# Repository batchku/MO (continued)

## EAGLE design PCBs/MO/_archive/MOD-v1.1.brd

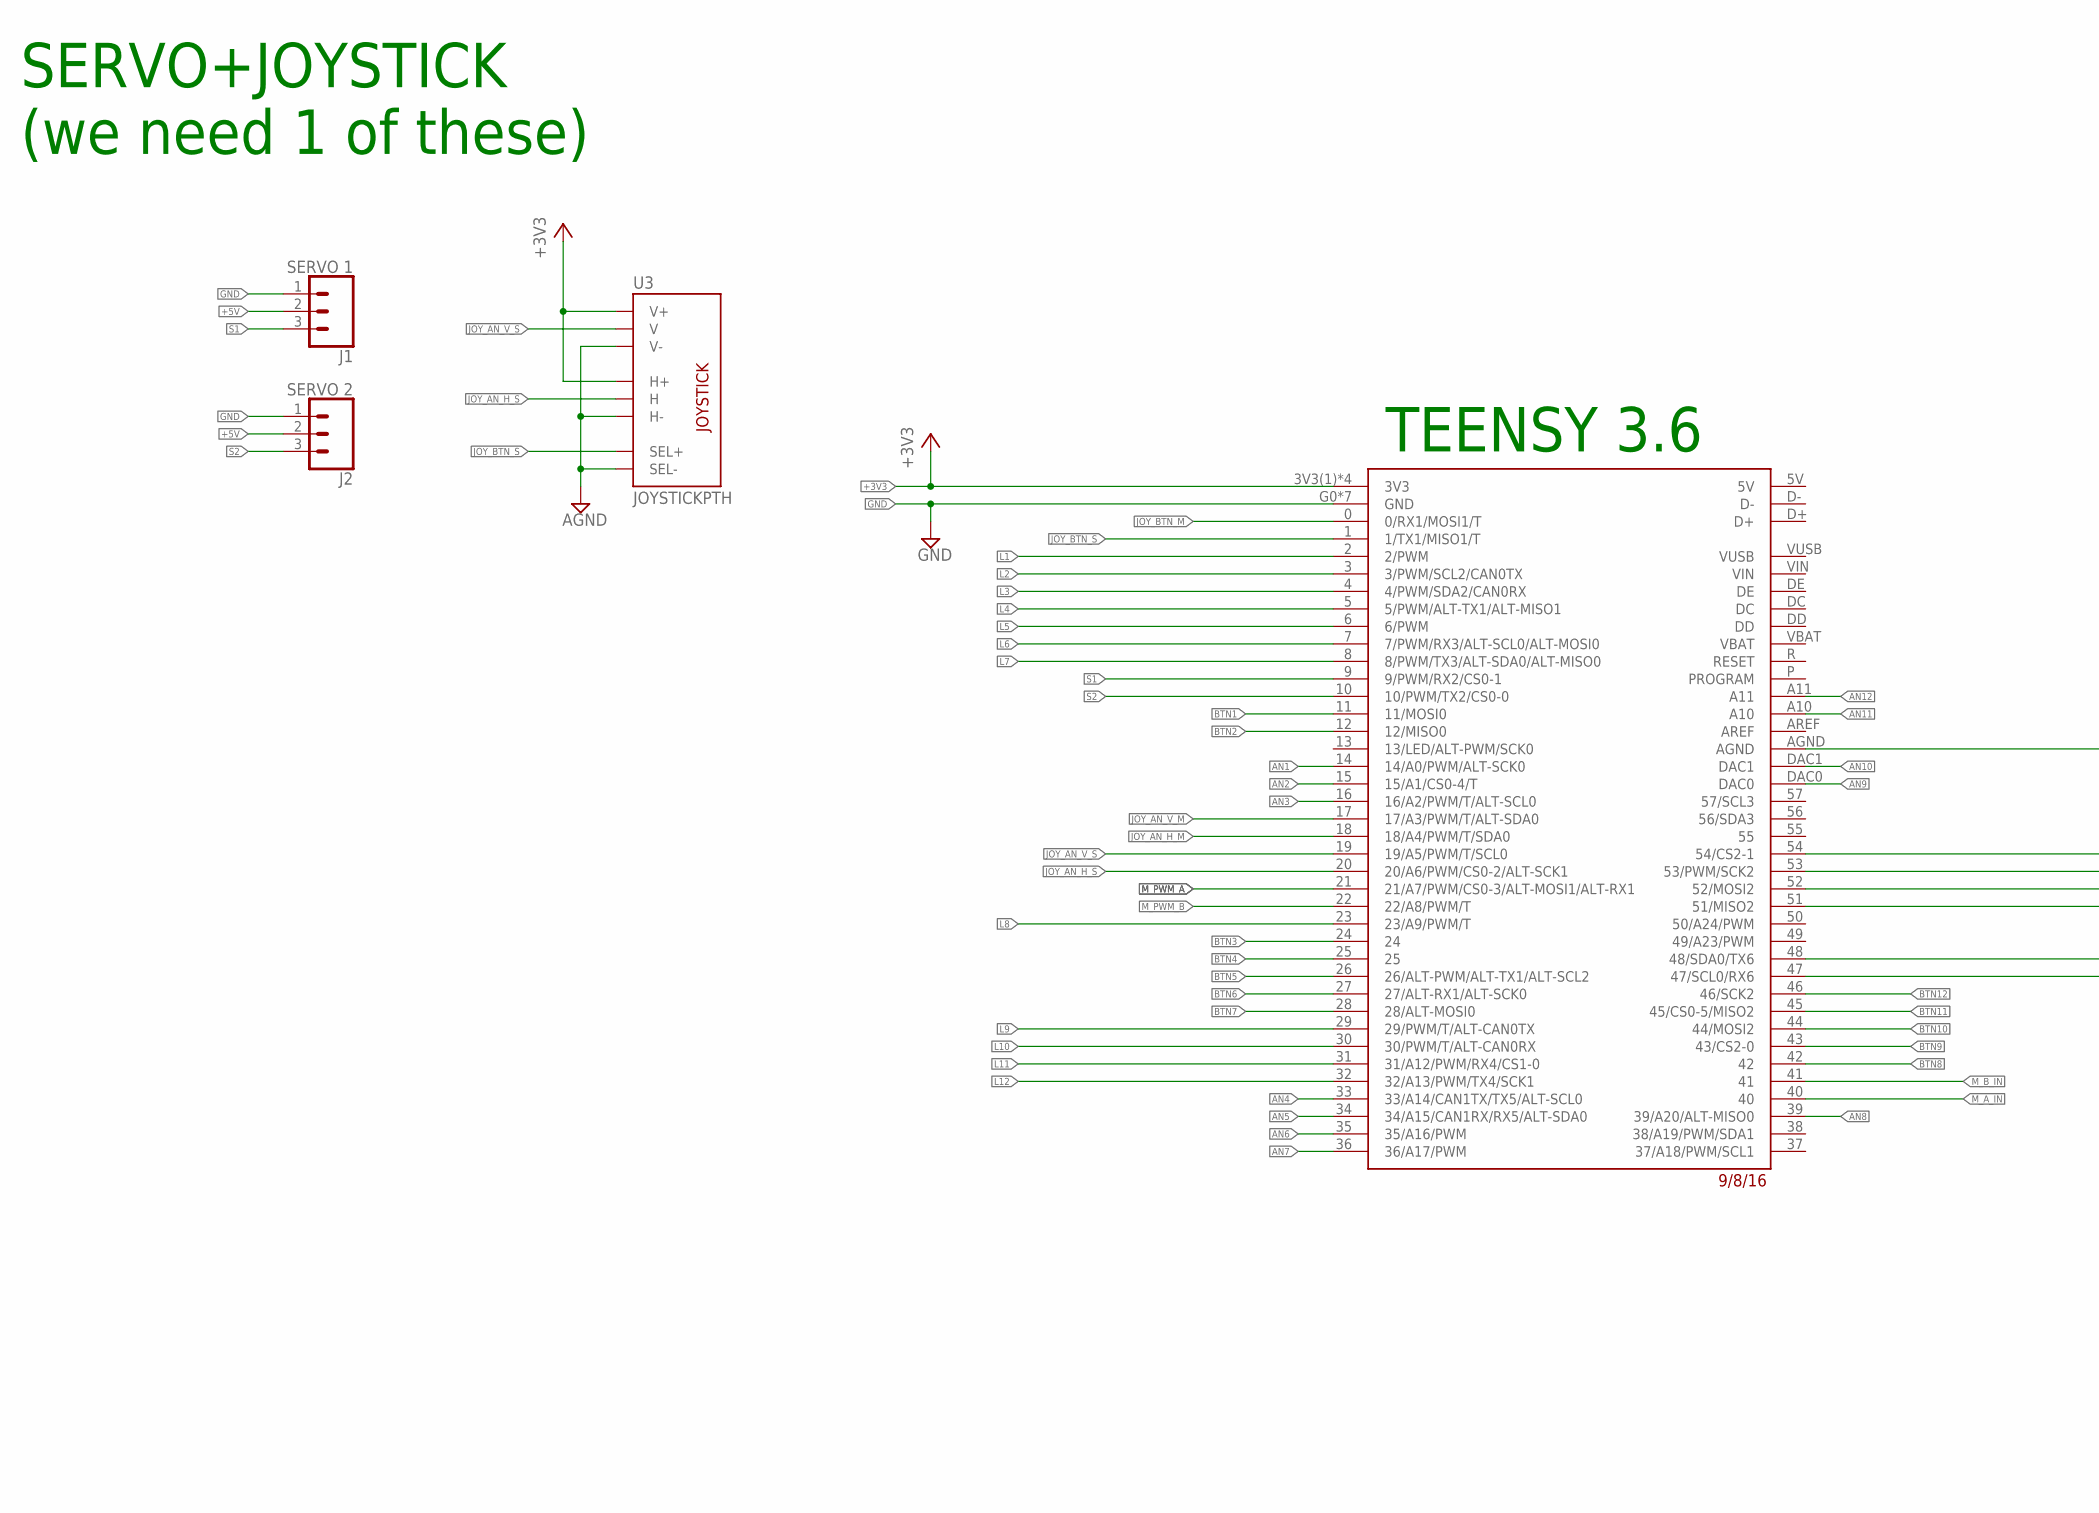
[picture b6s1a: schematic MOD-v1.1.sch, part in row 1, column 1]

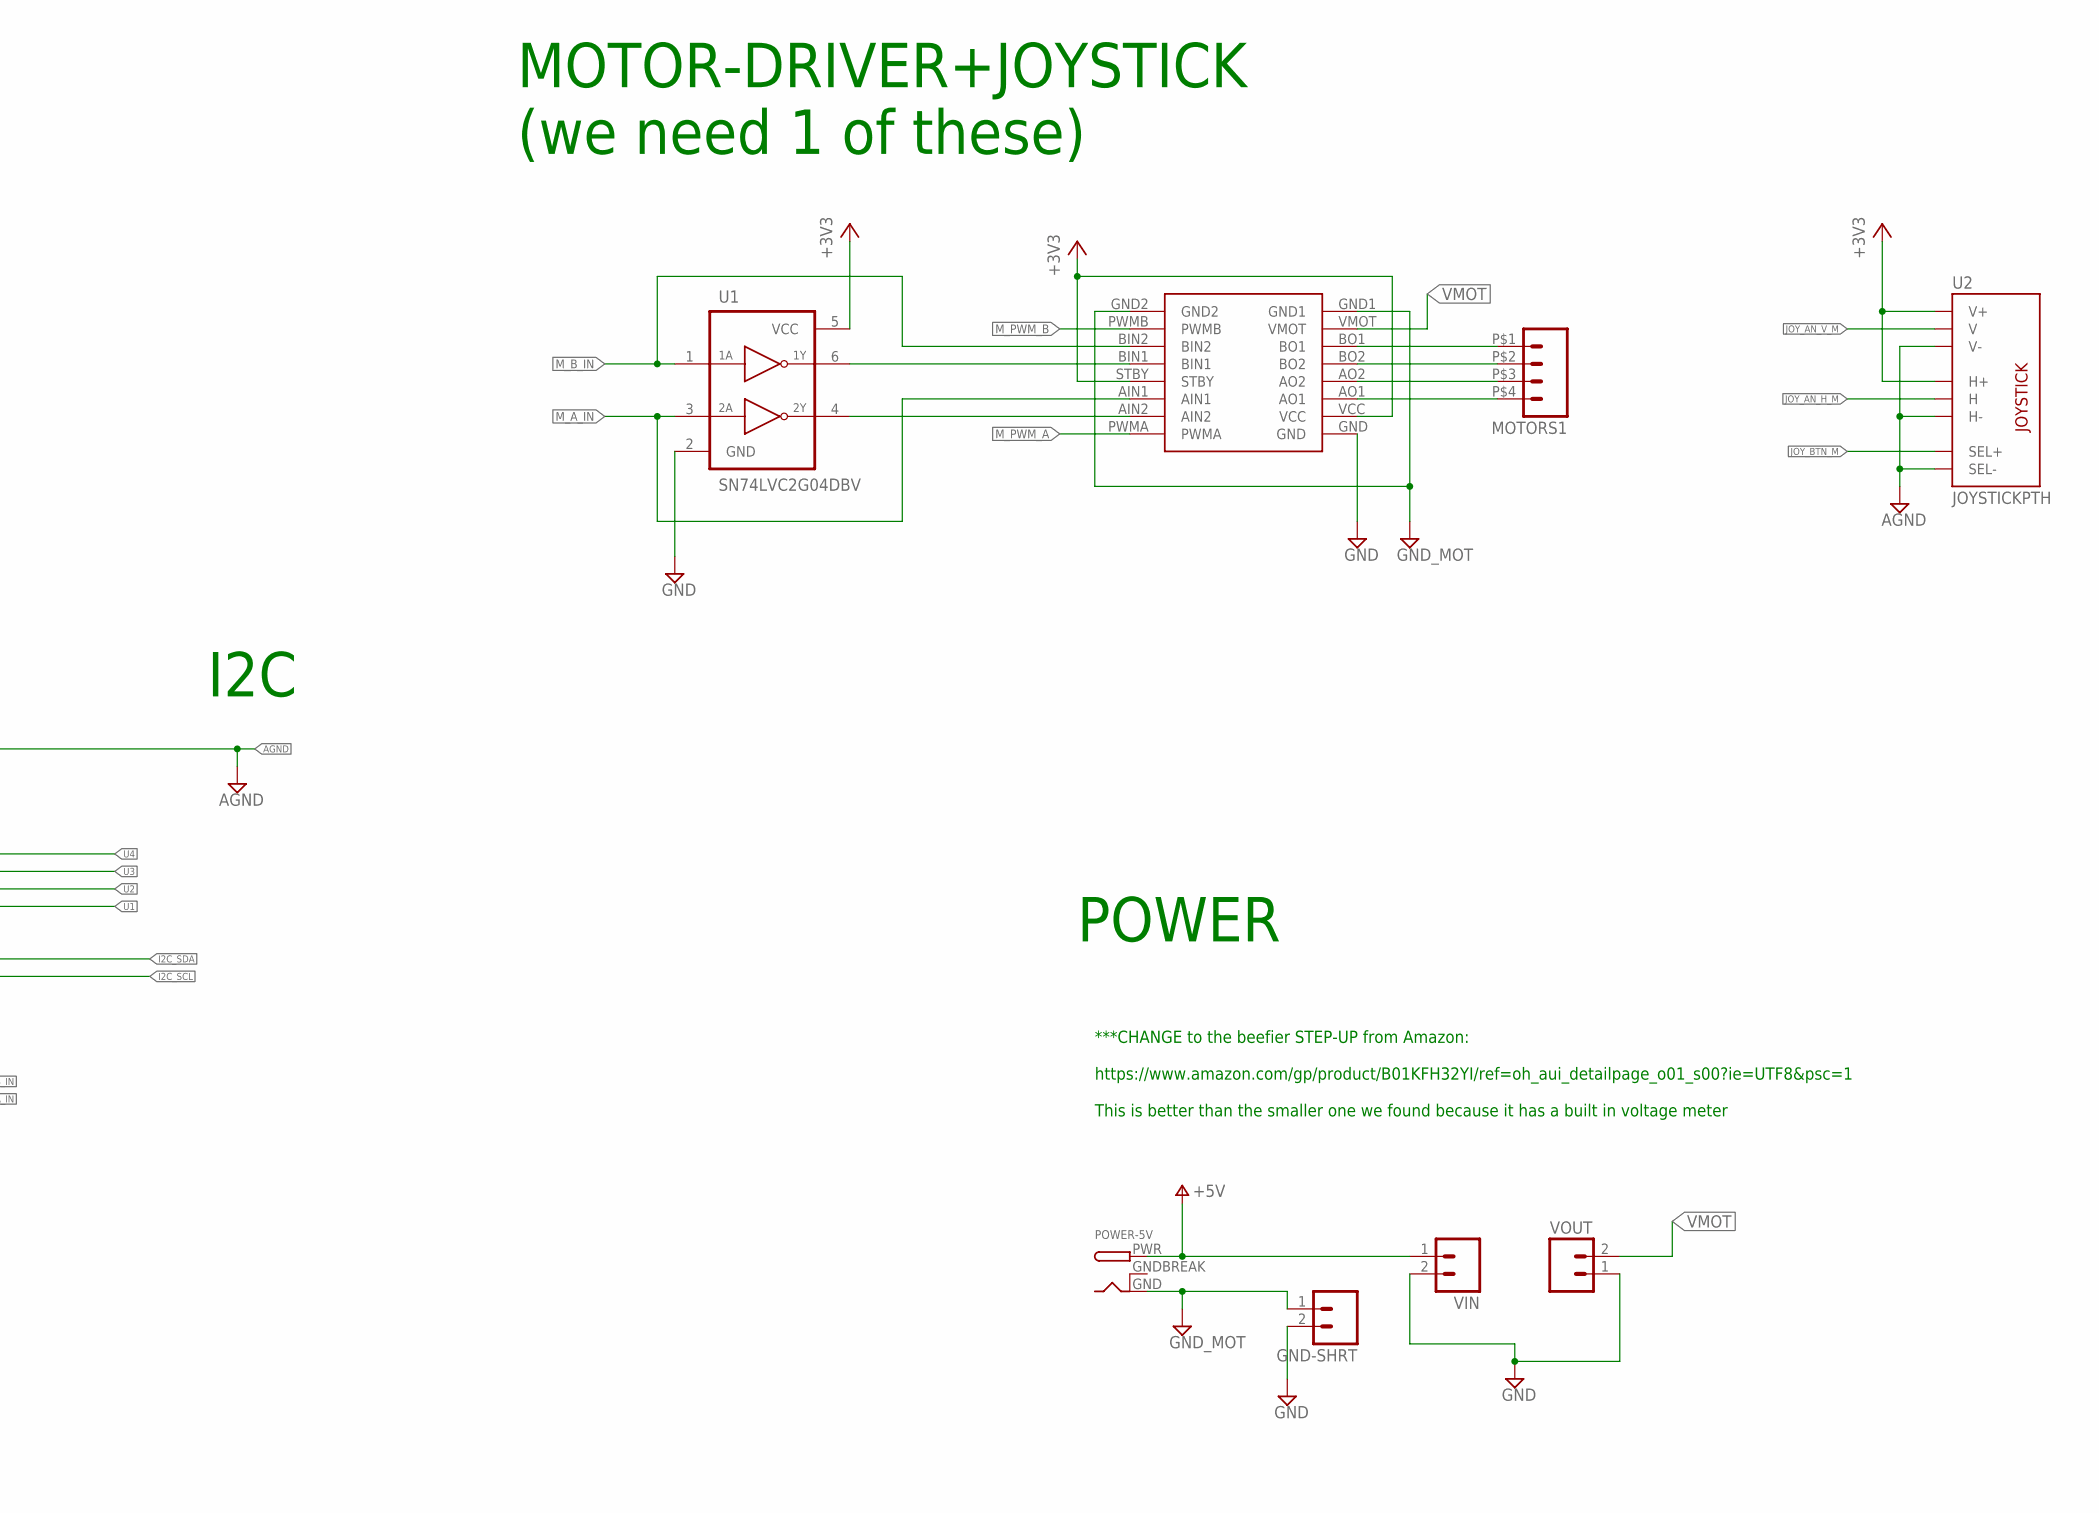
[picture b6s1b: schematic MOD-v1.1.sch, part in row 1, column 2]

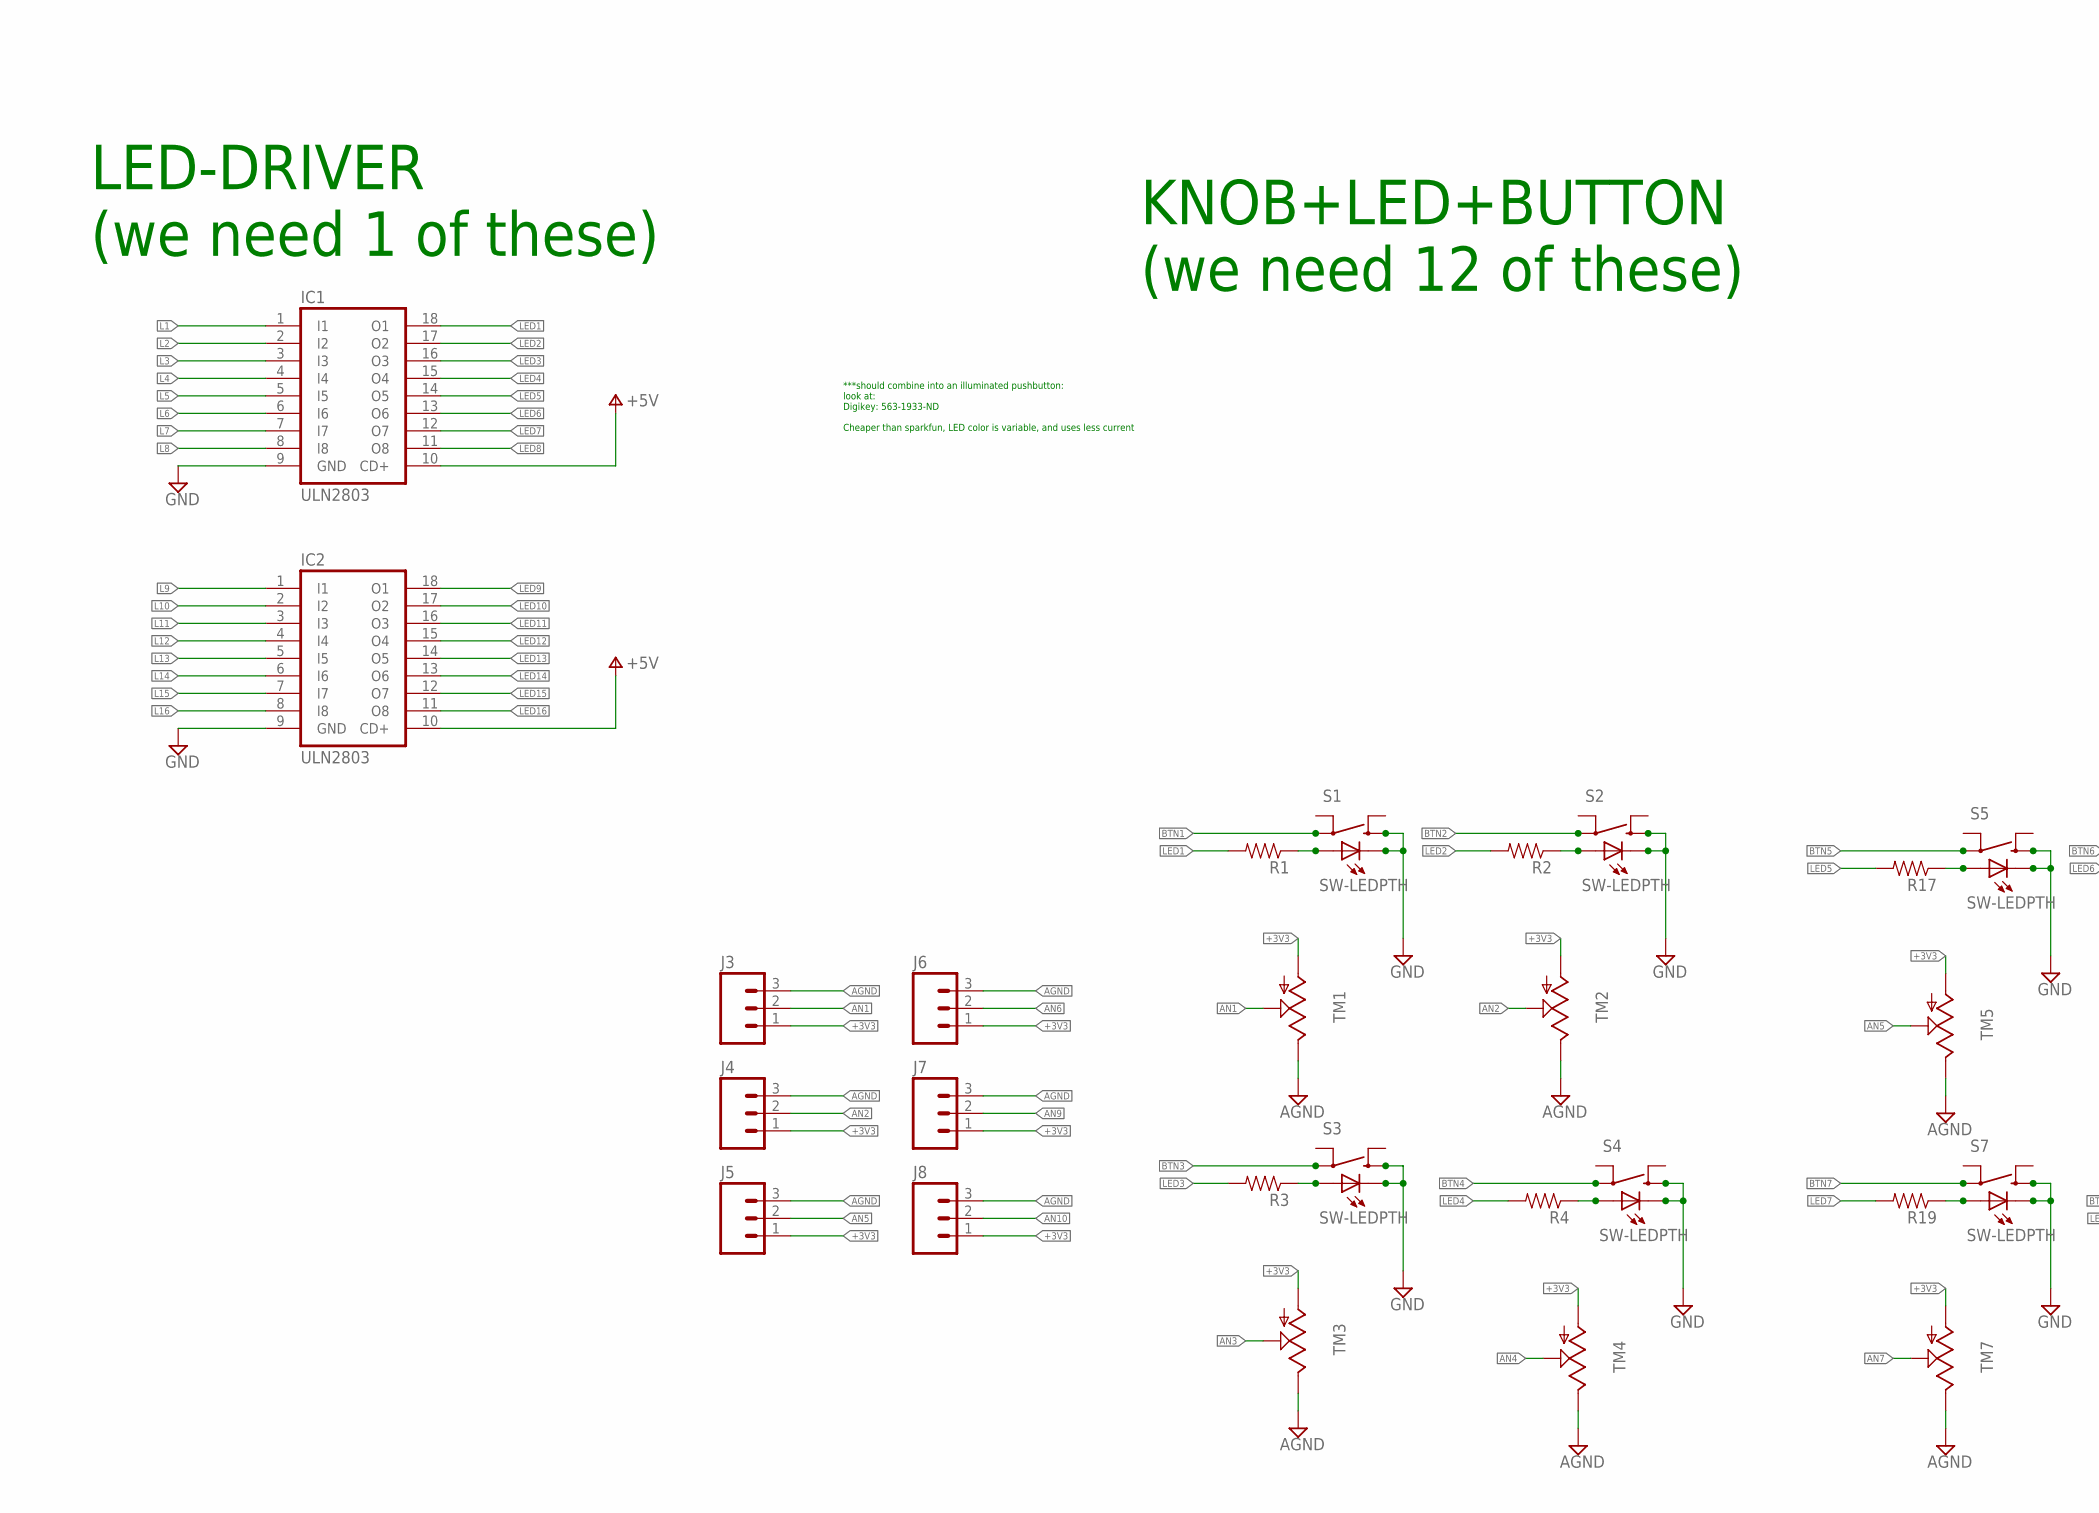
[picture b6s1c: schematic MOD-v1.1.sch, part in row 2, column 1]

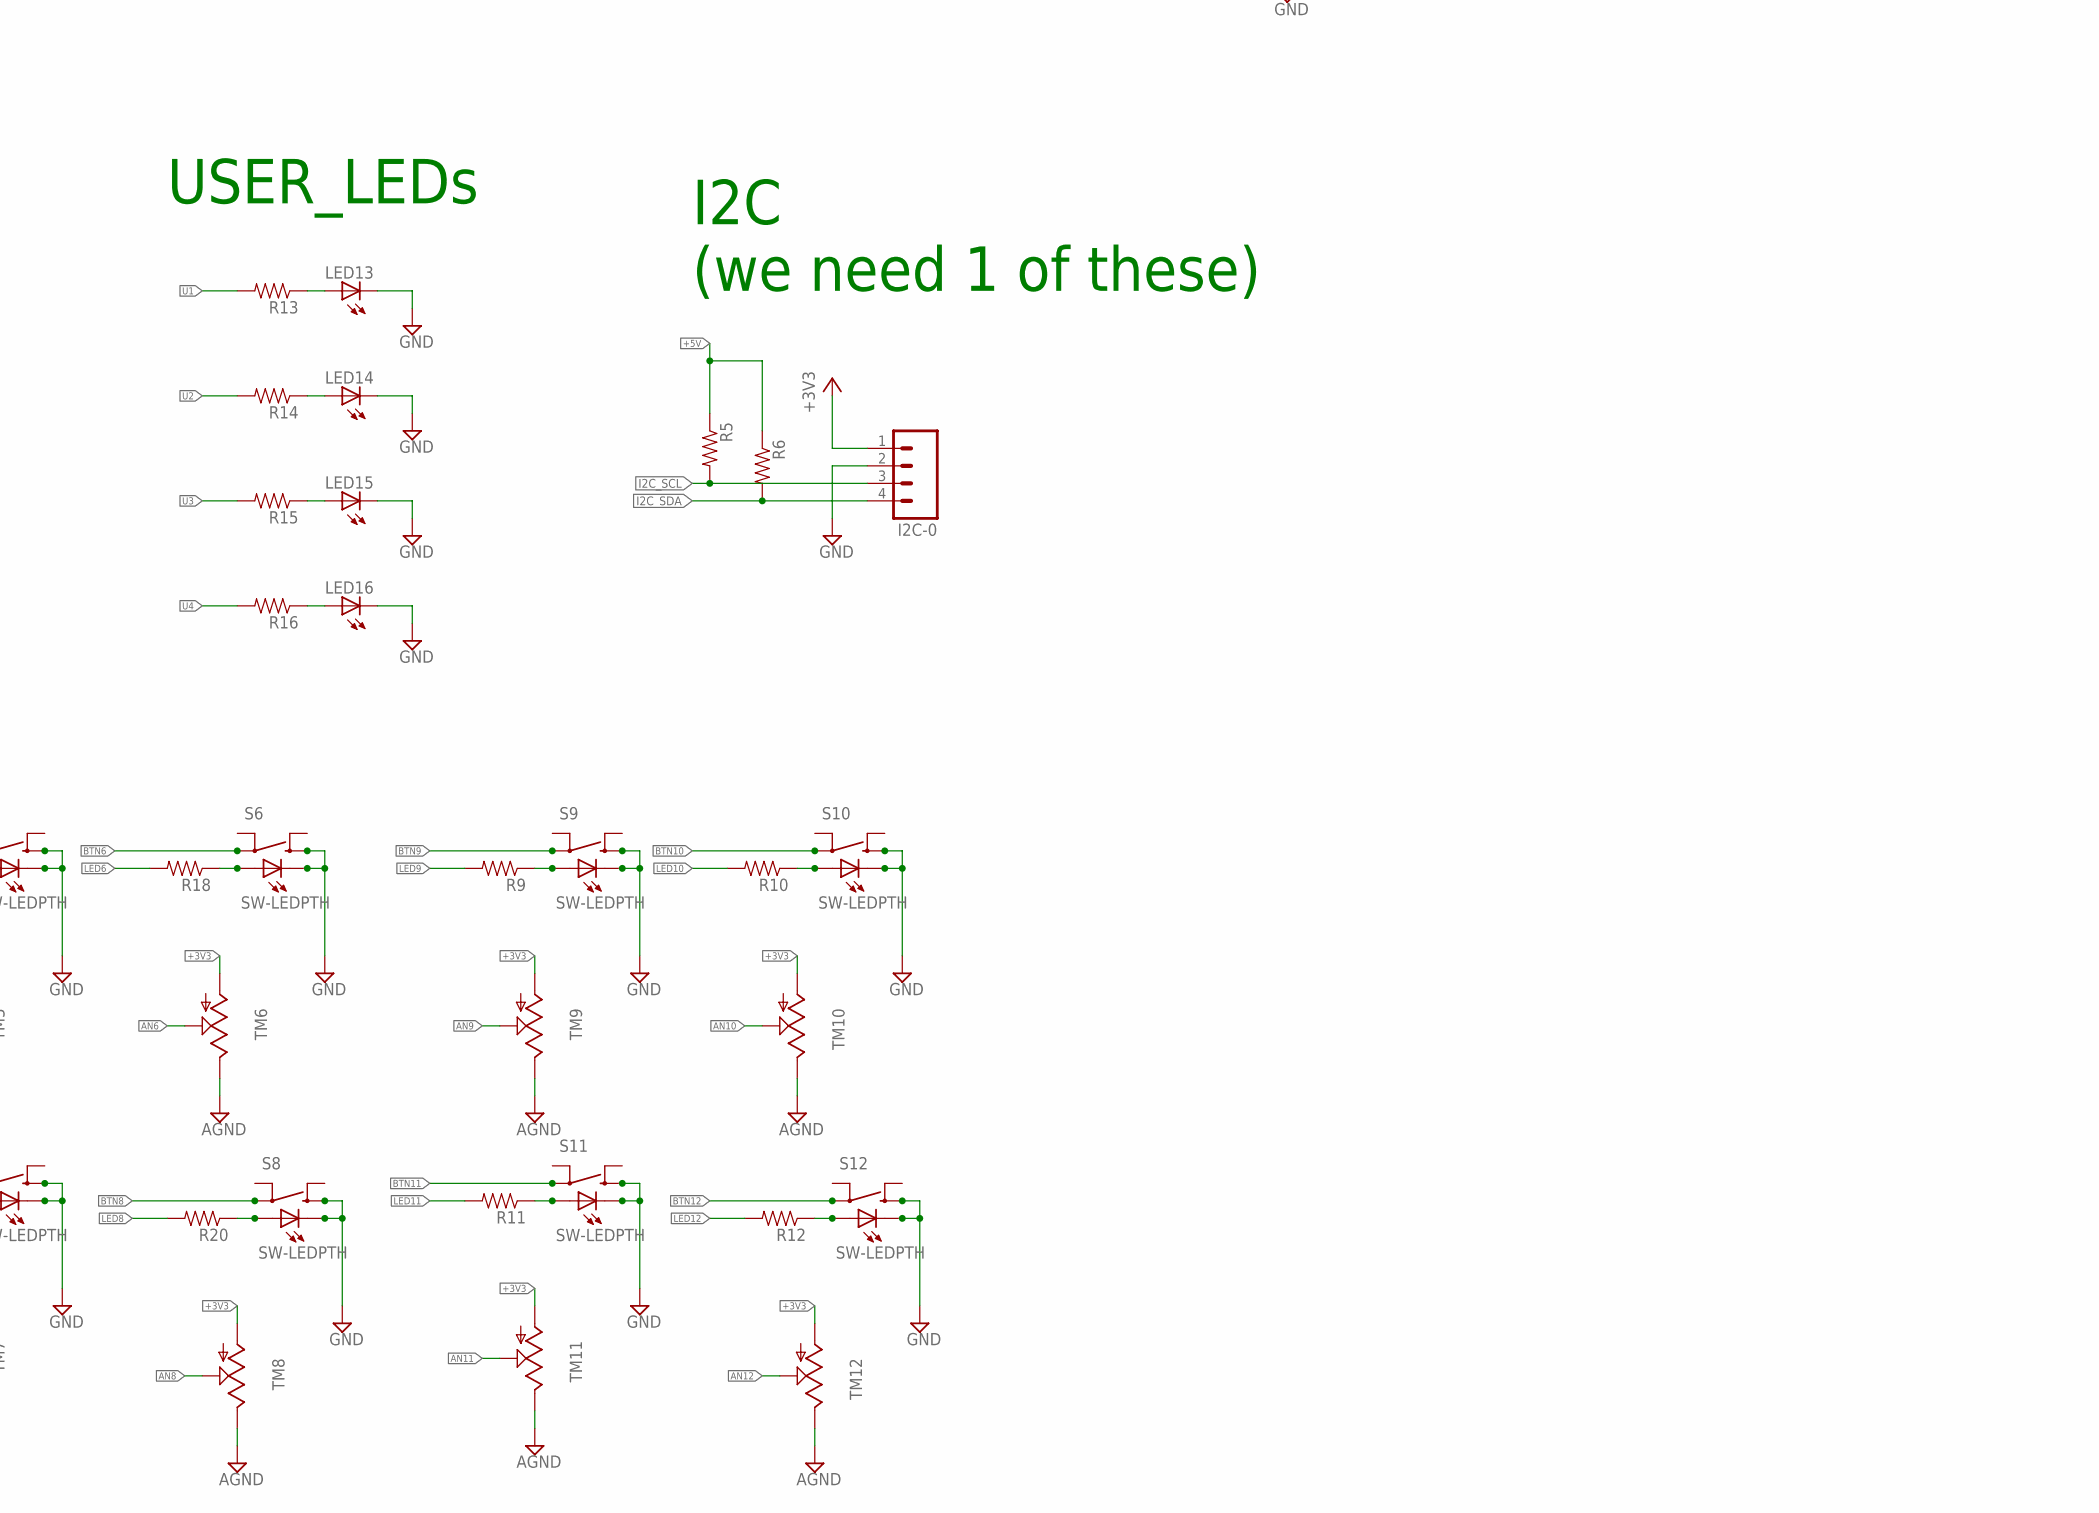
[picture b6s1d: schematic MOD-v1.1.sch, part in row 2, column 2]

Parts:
GND-SHRT: M02LOCK; 1X02_LOCK
I2C-0: M04LOCK; 1X04_LOCK
IC1, IC2: ULN2803; DIL18
J1: SERVO 1; 1X03_LOCK@1
J2: SERVO 2; 1X03_LOCK@1
J3, J4, J5, J6, J7, J8: M031X03_NO_SILK; 1X03_NO_SILK
LED13, LED14, LED15, LED16: LED3MM
MOTORS1: M04; SPRINGTERMINAL-2.54MM-4
POWER-5V: DCBARRELPTH; DCJACK_2MM_PTH
R1, R2, R3, R4, R5, R6, R9, R10, R11, R12, R13, R14, R15, R16, R17, R18, R19, R20: RESISTOREZ; AXIAL-0.3EZ
S1, S2, S3, S4, S5, S6, S7, S8, S9, S10, S11, S12: SW-LEDPTH; TR2-SWITCH-MOMENTARY-LED
TEENSY: TEENSY3_6--ALLPINS; T36
TM1, TM2, TM3, TM4, TM5, TM6, TM7, TM8, TM9, TM10, TM11, TM12: TRIM; TRIM-PCB-9MM
U1: SN74LVC2G04DBV; SOT23-6
U2, U3: JOYSTICKPTH; JOYSTICK
U$7: POLOLU_TB6612FNG
VIN: M02LOCK; 1X02_LOCK
VOUT: M02LOCK; 1X02_LOCK

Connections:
+3V3: I2C-0.1, J3.1, J4.1, J5.1, J6.1, J7.1, J8.1, TEENSY.3V3(1) (3V3), TEENSY.3V3(2) (3V3), TEENSY.3V3(3) (3V3), TEENSY.3V3(4) (3V3), TM1.1 (A), TM2.1 (A), TM3.1 (A), TM4.1 (A), TM5.1 (A), TM6.1 (A), TM7.1 (A), TM8.1 (A), TM9.1 (A), TM10.1 (A), TM11.1 (A), TM12.1 (A), U1.5 (VCC), U2.H1 (H+), U2.V1 (V+), U3.H1 (H+), U3.V1 (V+), U$7.STBY, U$7.VCC
+5V: IC1.10 (CD+), IC2.10 (CD+), J1.2, J2.2, POWER-5V.PWR, R5.P$1 (1), R6.P$1 (1), VIN.1
AGND: J3.3, J4.3, J5.3, J6.3, J7.3, J8.3, TEENSY.AGND, TM1.3 (E), TM2.3 (E), TM3.3 (E), TM4.3 (E), TM5.3 (E), TM6.3 (E), TM7.3 (E), TM8.3 (E), TM9.3 (E), TM10.3 (E), TM11.3 (E), TM12.3 (E), U2.B2A (SEL-), U2.H3 (H-), U2.V3 (V-), U3.B2A (SEL-), U3.H3 (H-), U3.V3 (V-)
AN1: J3.2, TEENSY.14 (14/A0/PWM/ALT-SCK0), TM1.2 (S)
AN2: J4.2, TEENSY.15 (15/A1/CS0-4/T), TM2.2 (S)
AN3: TEENSY.16 (16/A2/PWM/T/ALT-SCL0), TM3.2 (S)
AN4: TEENSY.33 (33/A14/CAN1TX/TX5/ALT-SCL0), TM4.2 (S)
AN5: J5.2, TEENSY.34 (34/A15/CAN1RX/RX5/ALT-SDA0), TM5.2 (S)
AN6: J6.2, TEENSY.35 (35/A16/PWM), TM6.2 (S)
AN7: TEENSY.36 (36/A17/PWM), TM7.2 (S)
AN8: TEENSY.39 (39/A20/ALT-MISO0), TM8.2 (S)
AN9: J7.2, TEENSY.DAC0, TM9.2 (S)
AN10: J8.2, TEENSY.DAC1, TM10.2 (S)
AN11: TEENSY.A10, TM11.2 (S)
AN12: TEENSY.A11, TM12.2 (S)
BTN1: S1.3, TEENSY.11 (11/MOSI0)
BTN2: S2.3, TEENSY.12 (12/MISO0)
BTN3: S3.3, TEENSY.24
BTN4: S4.3, TEENSY.25
BTN5: S5.3, TEENSY.26 (26/ALT-PWM/ALT-TX1/ALT-SCL2)
BTN6: S6.3, TEENSY.27 (27/ALT-RX1/ALT-SCK0)
BTN7: S7.3, TEENSY.28 (28/ALT-MOSI0)
BTN8: S8.3, TEENSY.42
BTN9: S9.3, TEENSY.43 (43/CS2-0)
BTN10: S10.3, TEENSY.44 (44/MOSI2)
BTN11: S11.3, TEENSY.45 (45/CS0-5/MISO2)
BTN12: S12.3, TEENSY.46 (46/SCK2)
GND: GND-SHRT.2, I2C-0.2, IC1.9 (GND), IC2.9 (GND), J1.1, J2.1, LED13.K (C), LED14.K (C), LED15.K (C), LED16.K (C), S1.1, S1.C, S2.1, S2.C, S3.1, S3.C, S4.1, S4.C, S5.1, S5.C, S6.1, S6.C, S7.1, S7.C, S8.1, S8.C, S9.1, S9.C, S10.1, S10.C, S11.1, S11.C, S12.1, S12.C, TEENSY.G0 (GND), TEENSY.G1 (GND), TEENSY.G2 (GND), TEENSY.G3 (GND), TEENSY.G4 (GND), TEENSY.G5 (GND), TEENSY.G6 (GND), U1.2 (GND), U$7.GND, VIN.2, VOUT.1
GNDBREAK: POWER-5V.GNDBREAK
GND_MOT: GND-SHRT.1, POWER-5V.GND, U$7.GND1, U$7.GND2
I2C_SCL: I2C-0.3, R5.P$2 (2), TEENSY.47 (47/SCL0/RX6)
I2C_SDA: I2C-0.4, R6.P$2 (2), TEENSY.48 (48/SDA0/TX6)
JOY_AN_H_M: TEENSY.18 (18/A4/PWM/T/SDA0), U2.H2 (H)
JOY_AN_H_S: TEENSY.20 (20/A6/PWM/CS0-2/ALT-SCK1), U3.H2 (H)
JOY_AN_V_M: TEENSY.17 (17/A3/PWM/T/ALT-SDA0), U2.V2 (V)
JOY_AN_V_S: TEENSY.19 (19/A5/PWM/T/SCL0), U3.V2 (V)
JOY_BTN_M: TEENSY.0 (0/RX1/MOSI1/T), U2.B1A (SEL+)
JOY_BTN_S: TEENSY.1 (1/TX1/MISO1/T), U3.B1A (SEL+)
L1: IC1.1 (I1), TEENSY.2 (2/PWM)
L2: IC1.2 (I2), TEENSY.3 (3/PWM/SCL2/CAN0TX)
L3: IC1.3 (I3), TEENSY.4 (4/PWM/SDA2/CAN0RX)
L4: IC1.4 (I4), TEENSY.5 (5/PWM/ALT-TX1/ALT-MISO1)
L5: IC1.5 (I5), TEENSY.6 (6/PWM)
L6: IC1.6 (I6), TEENSY.7 (7/PWM/RX3/ALT-SCL0/ALT-MOSI0)
L7: IC1.7 (I7), TEENSY.8 (8/PWM/TX3/ALT-SDA0/ALT-MISO0)
L8: IC1.8 (I8), TEENSY.23 (23/A9/PWM/T)
L9: IC2.1 (I1), TEENSY.29 (29/PWM/T/ALT-CAN0TX)
L10: IC2.2 (I2), TEENSY.30 (30/PWM/T/ALT-CAN0RX)
L11: IC2.3 (I3), TEENSY.31 (31/A12/PWM/RX4/CS1-0)
L12: IC2.4 (I4), TEENSY.32 (32/A13/PWM/TX4/SCK1)
L13: IC2.5 (I5)
L14: IC2.6 (I6)
L15: IC2.7 (I7)
L16: IC2.8 (I8)
LED1: IC1.18 (O1), R1.P$2 (2)
LED2: IC1.17 (O2), R2.P$2 (2)
LED3: IC1.16 (O3), R3.P$2 (2)
LED4: IC1.15 (O4), R4.P$2 (2)
LED5: IC1.14 (O5), R17.P$2 (2)
LED6: IC1.13 (O6), R18.P$2 (2)
LED7: IC1.12 (O7), R19.P$2 (2)
LED8: IC1.11 (O8), R20.P$2 (2)
LED9: IC2.18 (O1), R9.P$2 (2)
LED10: IC2.17 (O2), R10.P$2 (2)
LED11: IC2.16 (O3), R11.P$2 (2)
LED12: IC2.15 (O4), R12.P$2 (2)
LED13: IC2.14 (O5)
LED14: IC2.13 (O6)
LED15: IC2.12 (O7)
LED16: IC2.11 (O8)
M_A_IN: TEENSY.40, U1.3 (2A), U$7.AIN1
M_B_IN: TEENSY.41, U1.1 (1A), U$7.BIN2
M_PWM_A: TEENSY.21 (21/A7/PWM/CS0-3/ALT-MOSI1/ALT-RX1), U$7.PWMA
M_PWM_B: TEENSY.22 (22/A8/PWM/T), U$7.PWMB
unnamed: R1.P$1 (1), S1.A
unnamed: LED13.A, R13.P$1 (1)
unnamed: LED14.A, R14.P$1 (1)
unnamed: LED15.A, R15.P$1 (1)
unnamed: U1.6 (1Y), U$7.BIN1
unnamed: U1.4 (2Y), U$7.AIN2
unnamed: LED16.A, R16.P$1 (1)
unnamed: R2.P$1 (1), S2.A
unnamed: R3.P$1 (1), S3.A
unnamed: R4.P$1 (1), S4.A
unnamed: R9.P$1 (1), S9.A
unnamed: R10.P$1 (1), S10.A
unnamed: R11.P$1 (1), S11.A
unnamed: R12.P$1 (1), S12.A
unnamed: R17.P$1 (1), S5.A
unnamed: R18.P$1 (1), S6.A
unnamed: R19.P$1 (1), S7.A
unnamed: R20.P$1 (1), S8.A
unnamed: MOTORS1.P$1 (1), U$7.BO1
unnamed: MOTORS1.P$2 (2), U$7.BO2
unnamed: MOTORS1.P$3 (3), U$7.AO2
unnamed: MOTORS1.P$4 (4), U$7.AO1
S1: J1.3, TEENSY.9 (9/PWM/RX2/CS0-1)
S2: J2.3, TEENSY.10 (10/PWM/TX2/CS0-0)
U1: R13.P$2 (2), TEENSY.51 (51/MISO2)
U2: R14.P$2 (2), TEENSY.52 (52/MOSI2)
U3: R15.P$2 (2), TEENSY.53 (53/PWM/SCK2)
U4: R16.P$2 (2), TEENSY.54 (54/CS2-1)
VMOT: U$7.VMOT, VOUT.2

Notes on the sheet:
***should combine into an illuminated pushbutton: look at: Digikey: 563-1933-ND Cheaper than sparkfun, LED color is variable, and uses less current
KNOB+LED+BUTTON (we need 12 of these)
MOTOR-DRIVER+JOYSTICK (we need 1 of these)
***CHANGE to the beefier STEP-UP from Amazon: https://www.amazon.com/gp/product/B01KFH32YI/ref=oh_aui_detailpage_o01_s00?ie=UTF8&psc=1 This is better than the smaller one we found because it has a built in voltage meter
POWER
SERVO+JOYSTICK (we need 1 of these)
LED-DRIVER (we need 1 of these)
USER_LEDs
I2C (we need 1 of these)
I2C
TEENSY 3.6

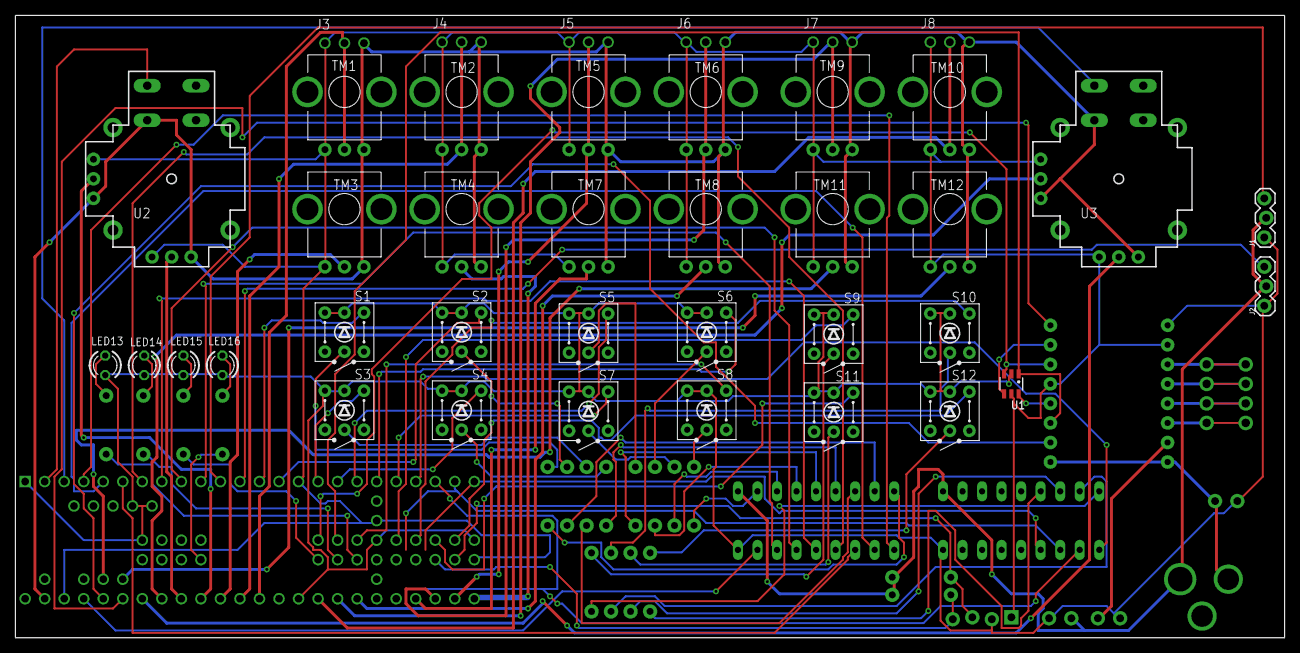
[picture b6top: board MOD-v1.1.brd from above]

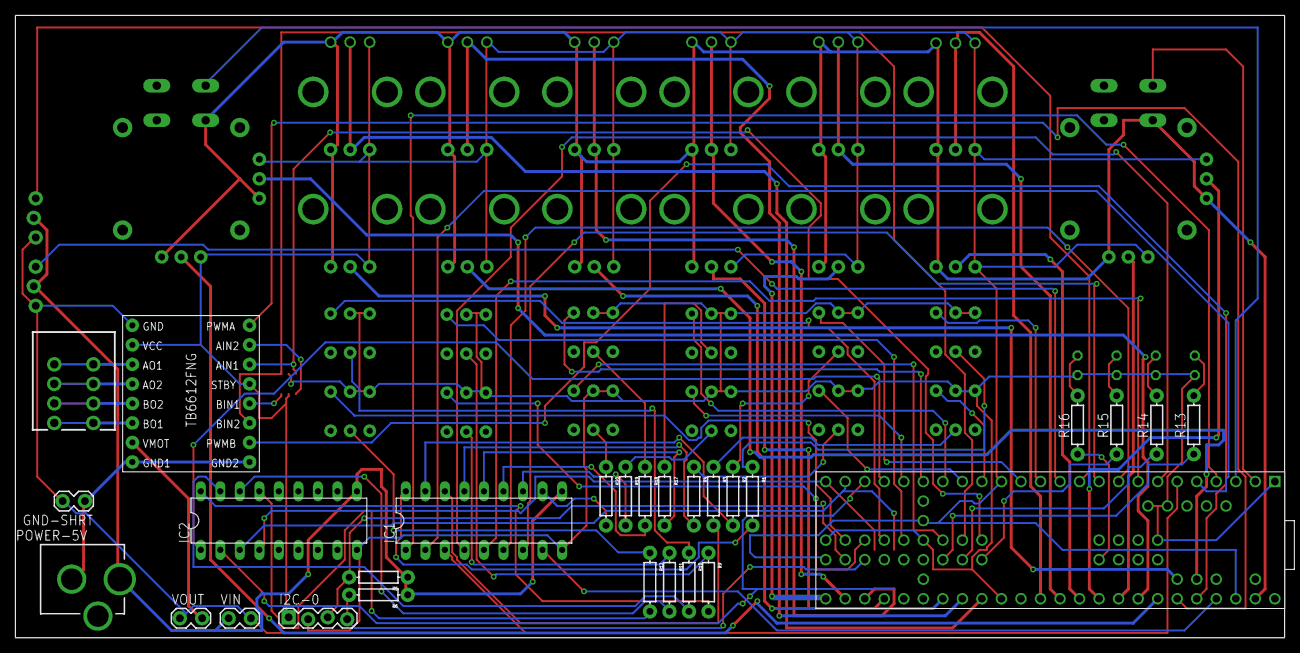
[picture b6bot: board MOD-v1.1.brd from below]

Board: 2 copper layers, 165.1 x 81.0 mm, 67 parts (28 on the bottom side), 94 nets.

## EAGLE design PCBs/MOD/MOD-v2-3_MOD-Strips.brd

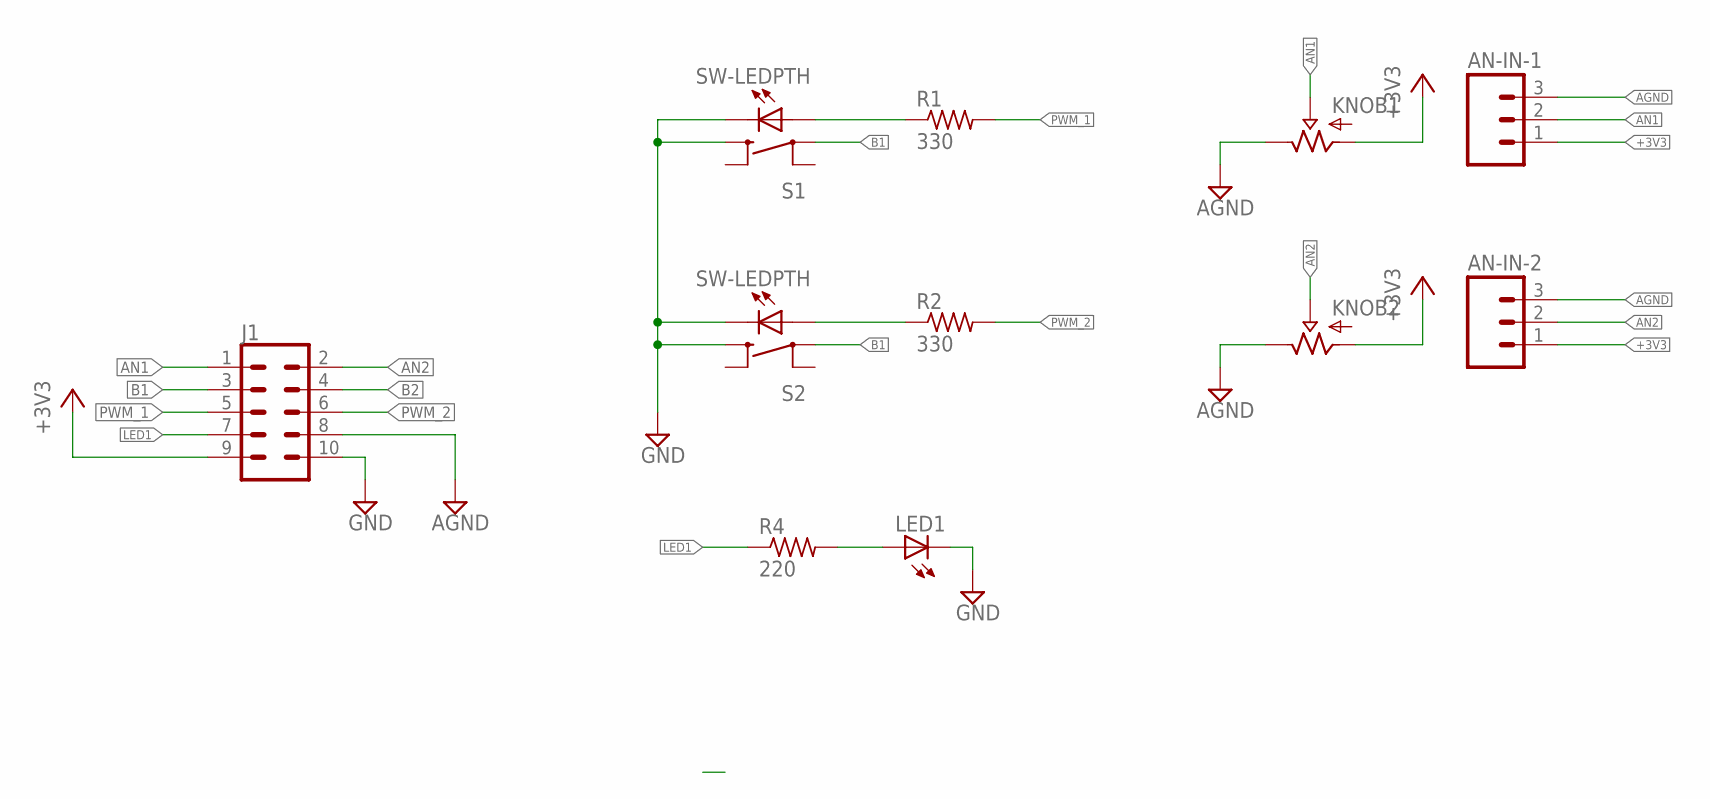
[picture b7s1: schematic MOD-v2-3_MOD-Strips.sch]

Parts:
AN-IN-1, AN-IN-2: M031X03_NO_SILK; 1X03_NO_SILK
J1: CONN_05X2SHD_LOCK; 2X5-SHROUDED_LOCK
KNOB1, KNOB2: POTALPHA_RD901; POT_ALPHA_RD901F-40-(L)R1
LED1: LED3MM
R1, R2: 330; 0204/5
R4: 220; 0204/7
S1, S2: SW-LEDPTH; TR2-SWITCH-MOMENTARY-LED

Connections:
+3V3: AN-IN-1.1, AN-IN-2.1, J1.9, KNOB1.1 (IN), KNOB2.1 (IN)
AGND: AN-IN-1.3, AN-IN-2.3, J1.8, KNOB1.3 (OUT), KNOB2.3 (OUT)
AN1: AN-IN-1.2, J1.1, KNOB1.2 (WIPER)
AN2: AN-IN-2.2, J1.2, KNOB2.2 (WIPER)
B1: J1.3, S1.3, S2.3
B2: J1.4
GND: J1.10, LED1.K (C), S1.1, S1.C, S2.1, S2.C
LED1: J1.7, R4.1
N1: LED1.A, R4.2
unnamed: R1.1, S1.A
unnamed: R2.1, S2.A
PWM_1: J1.5, R1.2
PWM_2: J1.6, R2.2

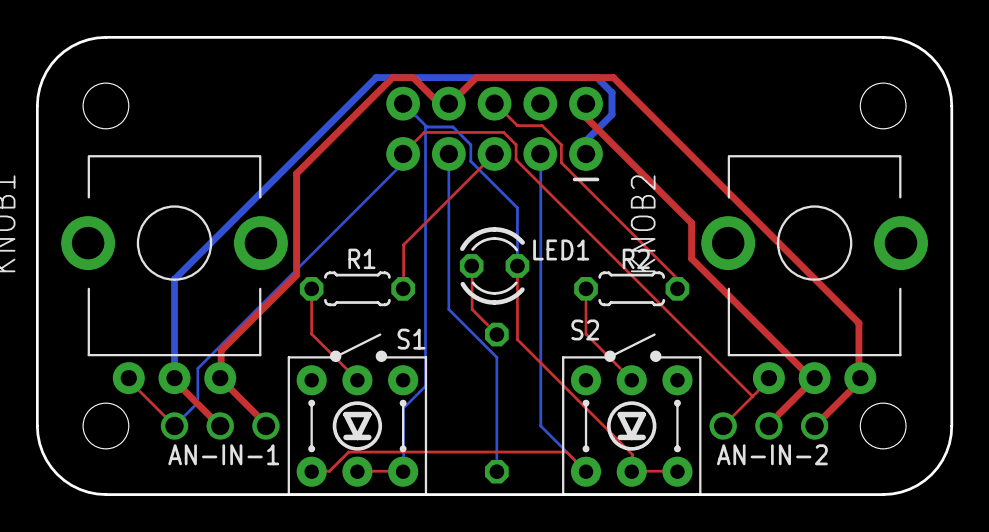
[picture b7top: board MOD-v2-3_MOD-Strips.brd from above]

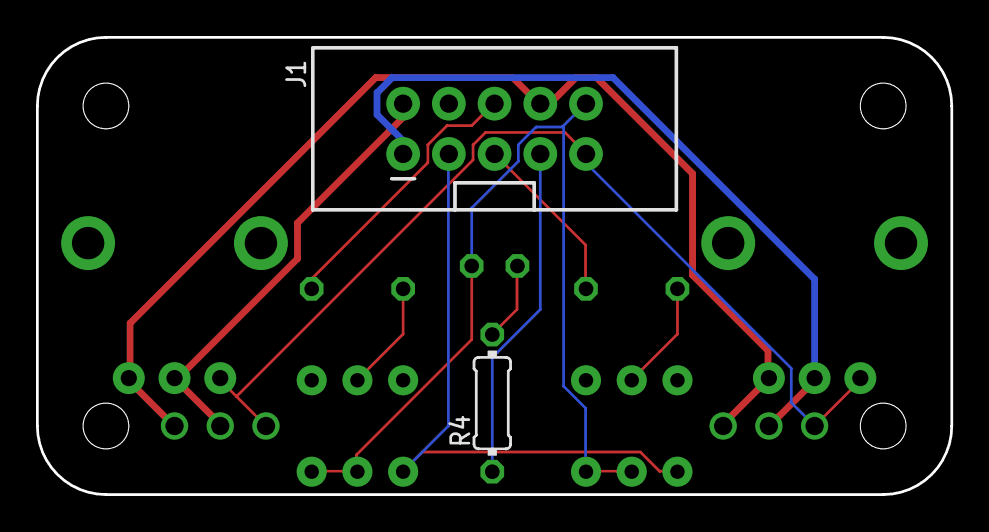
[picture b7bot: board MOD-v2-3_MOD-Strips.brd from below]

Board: 2 copper layers, 50.8 x 25.4 mm, 11 parts (2 on the bottom side), 12 nets.

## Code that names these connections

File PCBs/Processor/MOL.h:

//------------------------------------------------------
//Thiis file is automatically generated with pinlister.py
//------------------------------------------------------

const int LED3      = 0;
const int BTN5      = 1;
const int PWM2      = 2;
const int PWM1      = 3;
const int PWM4      = 4;
const int PWM3      = 5;
const int PWM5      = 6;
const int PWM6      = 7;
const int PWM8      = 8;
const int PWM7      = 9;
const int PWM9      = 10;
const int BTN6      = 11;
const int BTN3      = 12;
const int BTN16     = 13;
const int PWM12     = 14;
const int AN8       = 15;
const int PWM11     = 16;
const int PWM10     = 17;
const int AN10      = 18;
const int AN5       = 19;
const int AN3       = 20;
const int AN4       = 21;
const int AN1       = 22;
const int AN2       = 23;
const int BTN4      = 24;
const int BTN8      = 25;
const int BTN7      = 26;
const int BTN9      = 27;
const int BTN15     = 28;
const int PWM13     = 29;
const int PWM14     = 30;
const int JOYH2     = 31;
const int JOYV2     = 32;
const int S2        = 33;
const int S1        = 34;
const int M_PWMB    = 35;
const int M_PWMA    = 36;
const int PWM16     = 37;
const int PWM15     = 38;
const int AN6       = 39;
const int BTN10     = 40;
const int LED5      = 41;
const int BTN13     = 42;
const int LED6      = 43;
const int JOYB2     = 44;
const int M_INA     = 45;
const int M_INB     = 46;
const int JOYB1     = 47;
const int BTN12     = 48;
const int AN12      = 49;
const int AN11      = 50;
const int BTN14     = 51;
const int BTN11     = 52;
const int LED4      = 53;
const int BTN1      = 54;
const int LED1      = 55;
const int BTN2      = 56;
const int LED2      = 57;
const int JOYV1     = A10;
const int JOYH1     = A11;
const int AN7       = A21;
const int AN9       = A22;

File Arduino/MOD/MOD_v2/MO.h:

//------------------------------------------------------
//Thiis file is automatically generated with pinlister.py
//------------------------------------------------------

const int LED4      = 0;
const int BTN16     = 1;
const int PWM1      = 2;
const int PWM2      = 3;
const int PWM3      = 4;
const int PWM4      = 5;
const int PWM5      = 6;
const int PWM6      = 7;
const int PWM7      = 8;
const int PWM8      = 9;
const int PWM15     = 10;
const int BTN12     = 11;
const int BTN11     = 12;
const int BTN13     = 13;
const int PWM12     = 14;
const int AN4       = 15;
const int PWM14     = 16;
const int PWM16     = 17;
const int AN5       = 18;
const int AN6       = 19;
const int AN7       = 20;
const int AN8       = 21;
const int AN11      = 22;
const int AN12      = 23;
const int BTN10     = 24;
const int BTN9      = 25;
const int BTN8      = 26;
const int BTN7      = 27;
const int BTN6      = 28;
const int PWM10     = 29;
const int PWM13     = 30;
const int JOYH2     = 31;
const int JOYV2     = 32;
const int S1        = 33;
const int S2        = 34;
const int M_PWMB    = 35;
const int M_PWMA    = 36;
const int PWM9      = 37;
const int PWM11     = 38;
const int AN1       = 39;
const int BTN5      = 40;
const int LED2      = 41;
const int BTN3      = 42;
const int LED1      = 43;
const int JOYBTN2   = 44;
const int M_INA     = 45;
const int M_INB     = 46;
const int JOYBTN1   = 47;
const int BTN1      = 48;
const int AN9       = 49;
const int AN10      = 50;
const int BTN2      = 51;
const int BTN4      = 52;
const int LED3      = 53;
const int BTN14     = 54;
const int LED5      = 55;
const int BTN15     = 56;
const int LED6      = 57;
const int JOYV1     = A10;
const int JOYH1     = A11;
const int AN2       = A21;
const int AN3       = A22;
